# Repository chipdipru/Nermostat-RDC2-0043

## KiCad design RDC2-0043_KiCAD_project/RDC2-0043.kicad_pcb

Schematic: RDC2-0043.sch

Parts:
C1, C2, C6, C7, C8, C10, C11, C12, C13, C14, C15: 0,1мкФ; C_0603_HandSoldering
C3, C5: 2,2мкФ; C_0603_HandSoldering
C4: 0,01мкФ; C_0603_HandSoldering
C9, C16: 10мкФ; TantalC_SizeA_EIA-3216_HandSoldering_mm
DA1: LP2985-3.3; SOT-23-5
DD1: AT25xxx
DD2: STM32F042K6Tx; LQFP-32_7x7mm_Pitch0.8mm
HL2, HL4, HL5, HL6: 7SEGMENTS; Oasistek_7SegInd_smd
HL3: LED; LED_0603_HandSoldering
R1, R2, R3, R4, R5, R7, R8, R9, R10, R11, R12, R13, R25: 10k; R_0603_HandSoldering
R6: 330R; R_0603_HandSoldering
R14: 4k7; R_0603_HandSoldering
R15, R16, R17, R18, R19, R20, R21, R22: 330; R_0603_HandSoldering
R23, R24: 22R; R_0603_HandSoldering
SW1, SW2, SW3, SW4, SW5: SW_PUSH; TC-0120
VD1: USBLC6; SOT23-6L
VD2: D; SOD-123
VT1, VT2, VT3, VT4: BSS138; SOT-23
XP2: CONN_01X03; Clem_3Pos_P5
XP5, XP6: PLS-2; Pin_Header_Straight_1x02_mm
XP8: CONN_01X04; pin_header-4-1.5_pitch
XS1: USB_OTG; Micro_USB_ElecFreaks
XS2: PLS-2; Pin_Header_Straight_1x02_mm

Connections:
5V: C3.1, C11.1, DA1.1 (VIN), DA1.3 (ON/~OFF~), VD1.5, VD2.1, XP5.1
AIN0: C16.1, DD2.6, R14.1, XS2.1
DIG_1: DD2.14, R11.2, VT4.1
DIG_2: DD2.15, R10.2, VT3.1
DIG_3: DD2.29, R9.2, VT2.1
DIG_4: DD2.30, R8.2, VT1.1
DISPLAY_ON: C12.1, DD2.8, R25.1, SW1.1
EN_INPUT: DD2.20, R1.2, XP2.2
GND: C1.2, C2.2, C3.2, C4.2, C5.2, C6.2, C7.2, C8.2, C9.2, C10.2, C11.2, C12.2, C13.2, C14.2, C15.2, C16.2, DA1.2 (GND), DD1.4 (GND), DD2.16, DD2.32, HL3.1, R7.2, R8.1, R9.1, R10.1, R11.1, R13.1, SW1.2, SW2.2, SW3.2, SW4.2, SW5.2, VD1.2, VT1.2, VT2.2, VT3.2, VT4.2, XP2.3, XP5.2, XP8.4, XS1.5, XS1.6, XS2.2
LED_1: HL2.7, HL4.7, HL5.7, HL6.7, R21.2
LED_2: HL2.6, HL4.6, HL5.6, HL6.6, R17.2
LED_3: HL2.4, HL4.4, HL5.4, HL6.4, R19.2
LED_4: HL2.2, HL4.2, HL5.2, HL6.2, R15.2
LED_5: HL2.1, HL4.1, HL5.1, HL6.1, R20.2
LED_6: HL2.9, HL4.9, HL5.9, HL6.9, R18.2
LED_7: HL2.10, HL4.10, HL5.10, HL6.10, R22.2
LED_8: HL2.5, HL4.5, HL5.5, HL6.5, R16.2
unnamed: C4.1, DA1.4 (BP)
unnamed: C13.1, DD2.2, R4.1, SW4.1
unnamed: C1.1, DD2.3, R2.1, SW5.1
unnamed: DD2.7, R15.1
unnamed: DD2.9, R19.1
unnamed: DD2.10, R16.1
unnamed: DD2.11, R20.1
unnamed: DD2.12, R17.1
unnamed: DD2.13, R21.1
unnamed: DD2.18, R18.1
unnamed: DD2.19, R22.1
unnamed: DD2.21, R23.1
unnamed: DD2.22, R24.1
unnamed: DD2.31, R6.1, R7.1, XP6.1
unnamed: HL2.3, HL2.8, VT1.3
unnamed: HL3.2, R6.2
unnamed: HL4.3, HL4.8, VT2.3
unnamed: HL5.3, HL5.8, VT3.3
unnamed: HL6.3, HL6.8, VT4.3
unnamed: VD1.1, XP8.2, XS1.2
unnamed: VD1.3, XP8.3, XS1.3
unnamed: VD2.2, XP8.1, XS1.1
RST: C2.1, DD2.4
SPI_MISO: DD1.2 (MISO), DD2.27
SPI_MOSI: DD1.5 (MOSI), DD2.28
SPI_NSS: DD1.1 (~CS), DD2.25, R12.1
SPI_SCK: DD1.6 (SCK), DD2.26, R13.2
SWCLK: C14.1, DD2.24, R3.1, SW3.1
SWDIO: C15.1, DD2.23, R5.1, SW2.1
USB_DM: R23.2, VD1.6
USB_DP: R24.2, VD1.4
VDD: C5.1, C6.1, C7.1, C8.1, C9.1, C10.1, DA1.5 (VOUT), DD1.3 (~WP), DD1.7 (~HOLD), DD1.8 (VCC), DD2.1, DD2.5, DD2.17, R1.1, R2.2, R3.2, R4.2, R5.2, R12.2, R14.2, R25.2, XP2.1, XP6.2

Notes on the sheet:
DNP

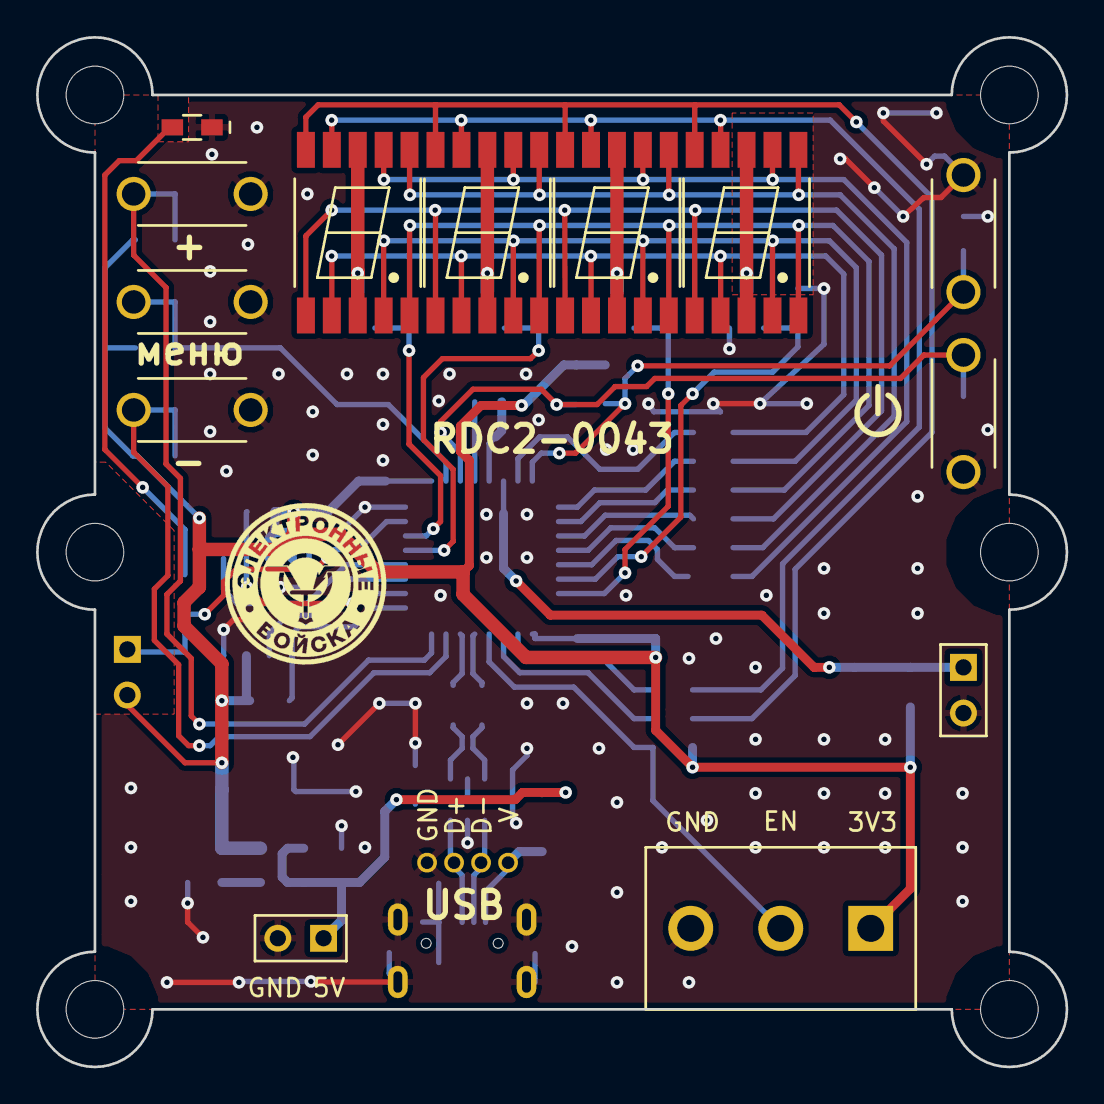
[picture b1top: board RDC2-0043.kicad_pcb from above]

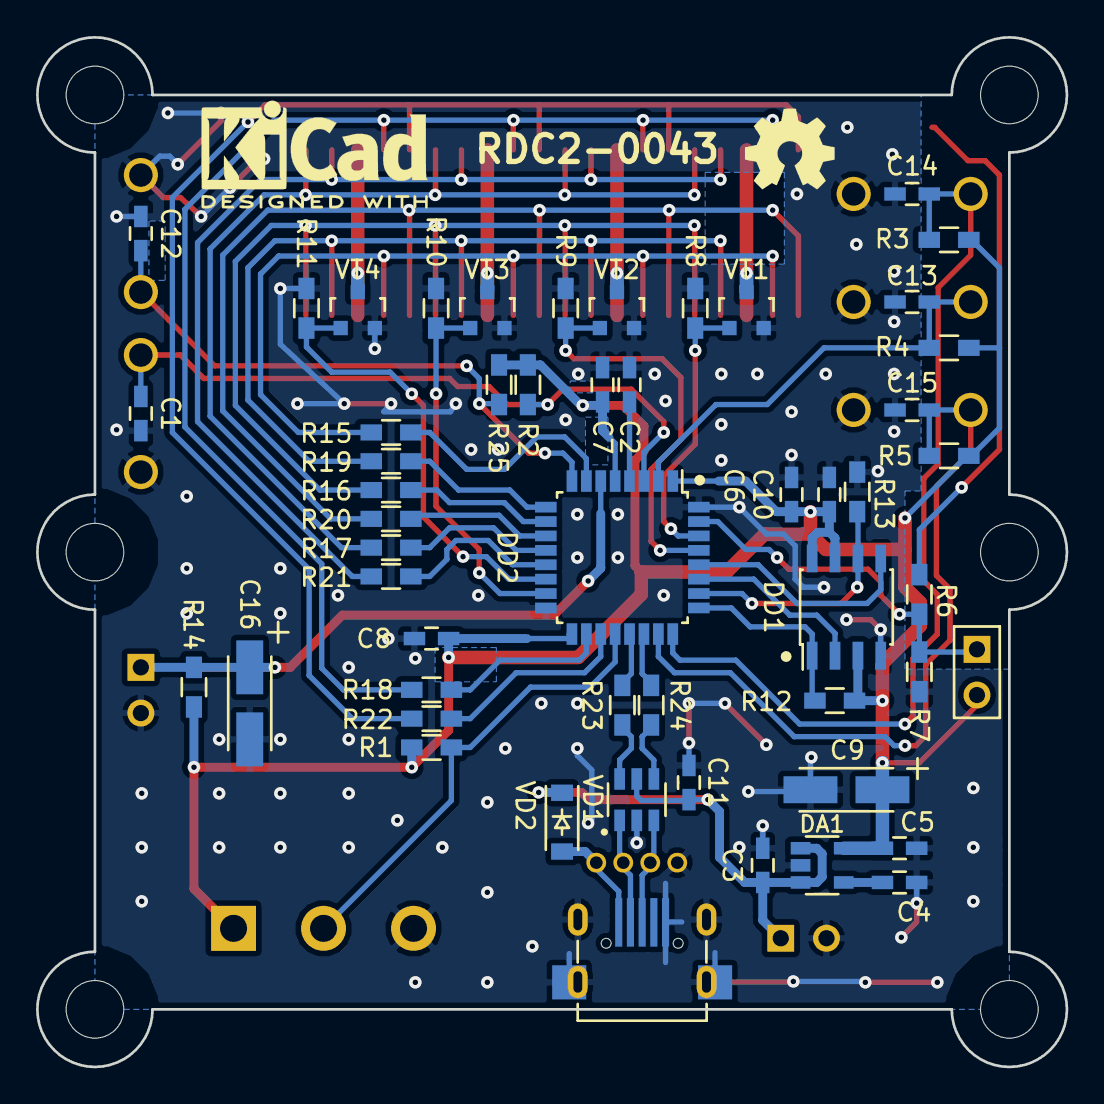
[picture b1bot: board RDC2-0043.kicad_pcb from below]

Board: 2 copper layers, 57.2 x 57.2 mm, 66 parts (53 on the bottom side), 49 nets.

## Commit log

2018-12-06 KiCad project
2018-12-06 Software
2018-12-06 dfu & hex files
2018-12-06 IAR project
